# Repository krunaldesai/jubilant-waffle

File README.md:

# jubilant-waffle
HW/SW for PAC-USWHS002-WF-2 replacement based on m5stack AtomS3 mini and ESPhome

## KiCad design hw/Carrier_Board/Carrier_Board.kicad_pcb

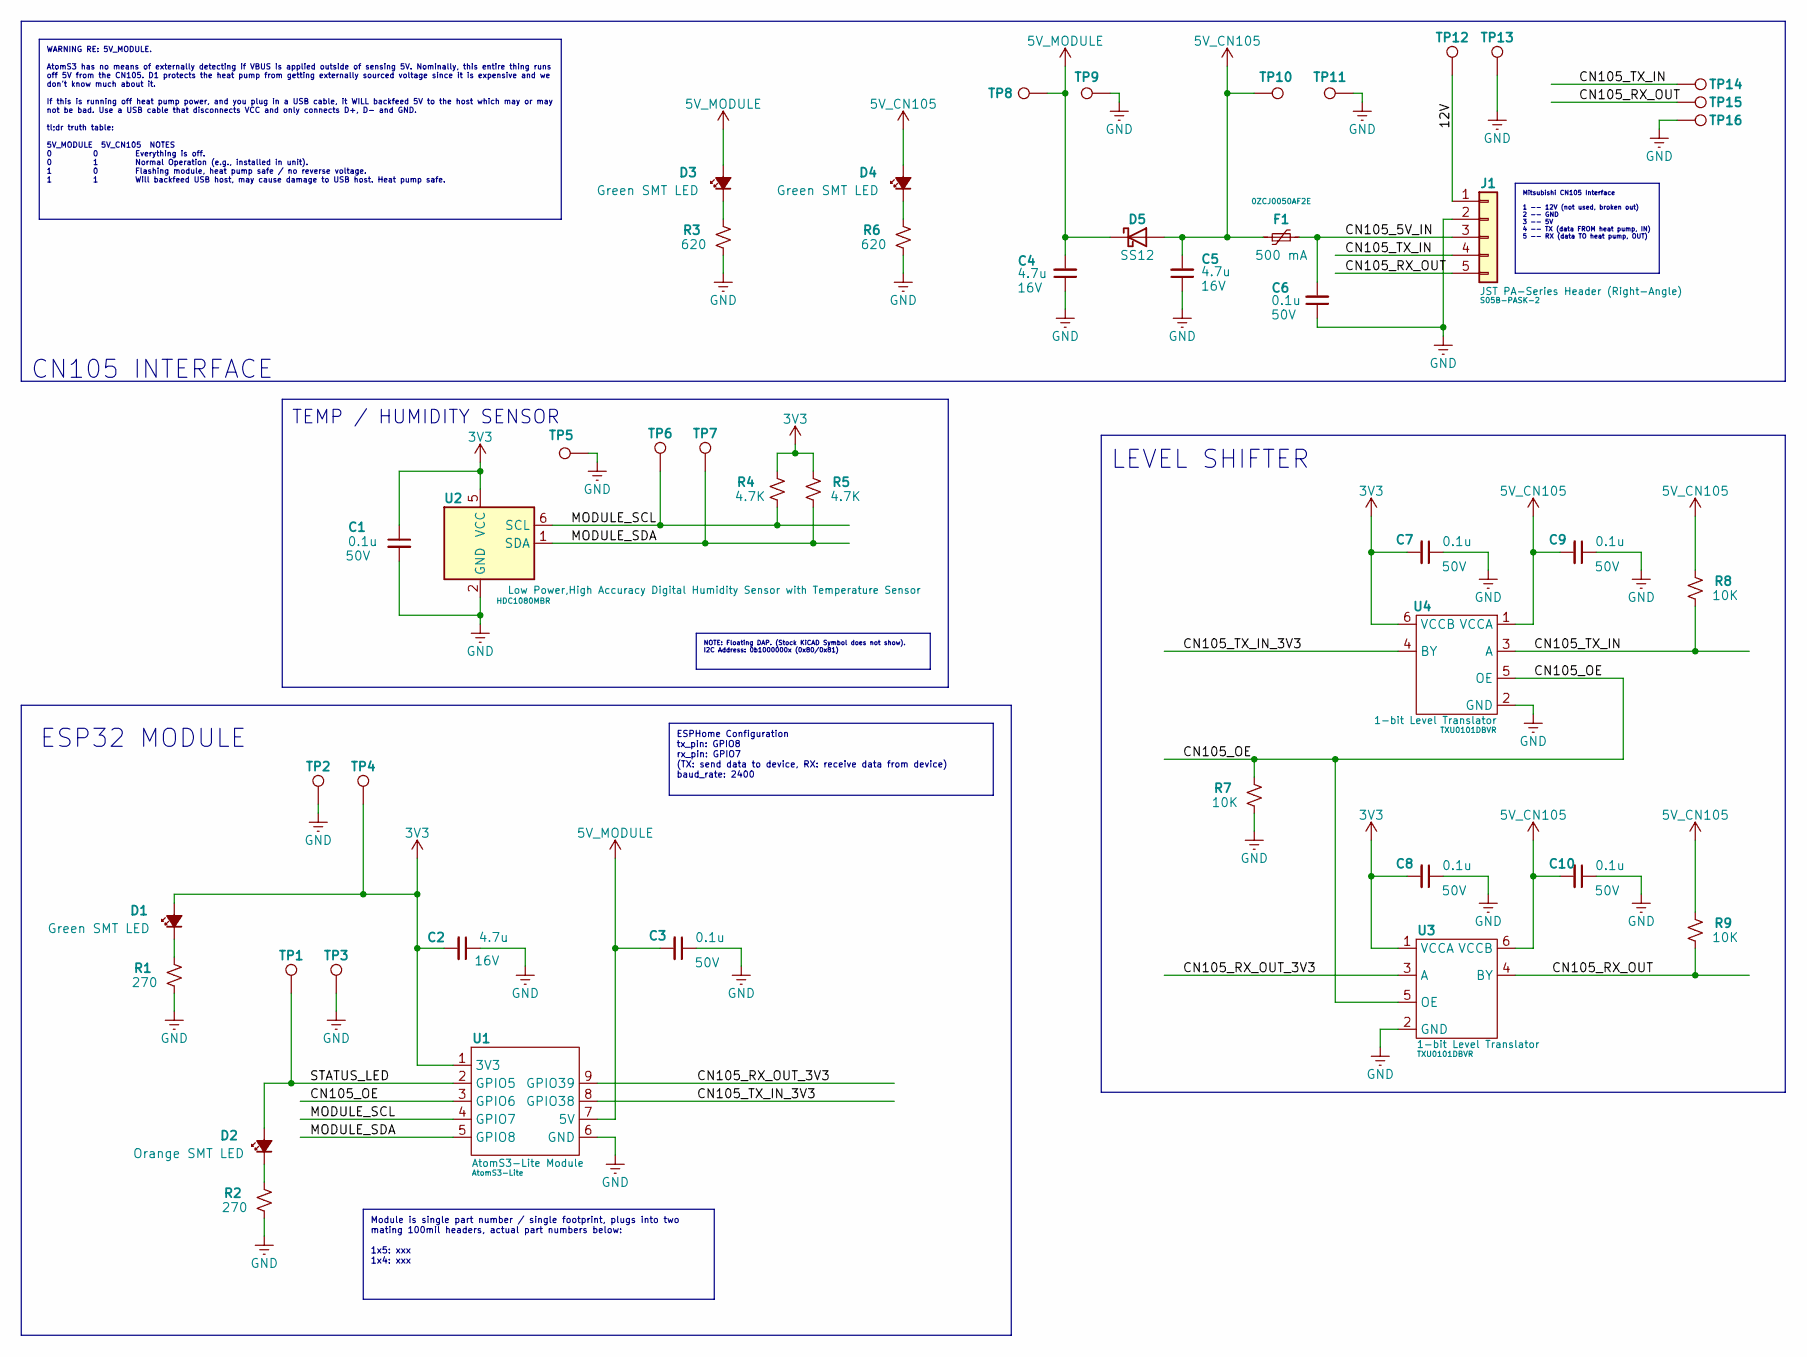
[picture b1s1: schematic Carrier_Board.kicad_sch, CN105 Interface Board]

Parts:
C1, C3, C6, C7, C8, C9, C10: 0.1u; C_0603_1608Metric_Pad1.08x0.95mm_HandSolder; Voltage 50V; ManufacturerPartNumber C0603C104K5RAC7411
C2, C4, C5: 4.7u; C_0805_2012Metric_Pad1.18x1.45mm_HandSolder; Voltage 16V; ManufacturerPartNumber GRM21BR71C475KE51L
D1, D3, D4: LED_Small_Filled; LED_0603_1608Metric_Pad1.05x0.95mm_HandSolder; ManufacturerPartNumber LTST-C190GKT
D2: LED_Small_Filled; LED_0603_1608Metric_Pad1.05x0.95mm_HandSolder; ManufacturerPartNumber LTST-C190AKT
D5: SS12; D_SMA; ManufacturerPartNumber SS12
F1: 500 mA; Fuse_1206_3216Metric_Pad1.42x1.75mm_HandSolder; ManufacturerPartNumber 0ZCJ0050AF2E
J1: JST PA-Series Header (Right-Angle); JST_PA_S05B; ManufacturerPartNumber S05B-PASK-2
R1, R2: 270; R_0603_1608Metric_Pad0.98x0.95mm_HandSolder; ManufacturerPartNumber ERJ-3GEYJ271V
R3, R6: 620; R_0603_1608Metric_Pad0.98x0.95mm_HandSolder; ManufacturerPartNumber ERJ-3GEYJ621V
R4, R5: 4.7K; R_0603_1608Metric_Pad0.98x0.95mm_HandSolder; ManufacturerPartNumber ERJ-3GEYJ472V
R7, R8, R9: 10K; R_0603_1608Metric_Pad0.98x0.95mm_HandSolder; ManufacturerPartNumber ERJ-3GEYJ103V
TP1, TP2, TP3, TP4, TP5, TP6, TP7, TP8, TP9, TP10, TP11, TP12, TP13, TP14, TP15, TP16: TestPoint; TestPoint_Keystone_5000-5004_Miniature
U1: Atom_S3-Lite; ManufacturerPartNumber AtomS3-Lite
U2: HDC1080; Texas_PWSON-N6; ManufacturerPartNumber HDC1080MBR
U3, U4: SOT-23-6_Handsoldering; ManufacturerPartNumber TXU0101DBVR

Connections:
3V3: C1.1, C2.2, C7.2, C8.2, D1.2 (A), R4.1, R5.1, TP4.1, U1.1 (3V3), U2.5 (VCC), U3.1 (VCCA), U4.6 (VCCB)
5V_CN105: C5.2, C9.2, C10.2, D4.2 (A), D5.2 (A), F1.1, R8.1, R9.1, TP10.1, U3.6 (VCCB), U4.1 (VCCA)
5V_MODULE: C3.2, C4.2, D3.2 (A), D5.1 (K), TP8.1, U1.7 (5V)
/12V: J1.1, TP12.1
/CN105_5V_IN: C6.2, F1.2, J1.3
/CN105_OE: R7.1, U1.3 (GPIO6), U3.5 (OE), U4.5 (OE)
/CN105_RX_OUT: J1.5, R9.2, TP15.1, U3.4 (BY)
/CN105_RX_OUT_3V3: U1.9 (GPIO39), U3.3 (A)
/CN105_TX_IN: J1.4, R8.2, TP14.1, U4.3 (A)
/CN105_TX_IN_3V3: U1.8 (GPIO38), U4.4 (BY)
/MODULE_SCL: R4.2, TP6.1, U1.4 (GPIO7), U2.6 (SCL)
/MODULE_SDA: R5.2, TP7.1, U1.5 (GPIO8), U2.1 (SDA)
/STATUS_LED: D2.2 (A), TP1.1, U1.2 (GPIO5)
GND: C1.2, C2.1, C3.1, C4.1, C5.1, C6.1, C7.1, C8.1, C9.1, C10.1, J1.2, R1.2, R2.2, R3.2, R6.2, R7.2, TP2.1, TP3.1, TP5.1, TP9.1, TP11.1, TP13.1, TP16.1, U1.6 (GND), U2.2 (GND), U3.2 (GND), U4.2 (GND)
unnamed: D1.1 (K), R1.1
unnamed: D2.1 (K), R2.1
unnamed: D3.1 (K), R3.1
unnamed: D4.1 (K), R6.1

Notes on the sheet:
LEVEL SHIFTER
TEMP / HUMIDITY SENSOR
ESP32 MODULE
CN105 INTERFACE
NOTE: Floating DAP. (Stock KiCAD Symbol does not show). I2C Address: 0b1000000x (0x80/0x81)
ESPHome Configuration tx_pin: GPIO8 rx_pin: GPIO7 (TX: send data to device, RX: receive data from device) baud_rate: 2400
Module is single part number / single footprint, plugs into two mating 100mil headers, actual part numbers below: 1x5: xxx 1x4: xxx
WARNING RE: 5V_MODULE. AtomS3 has no means of externally detecting if VBUS is applied outside of sensing 5V. Nominally, this entire thing runs off 5V from the CN105. D1 protects the heat pump from getting externally sourced voltage since it is expensive and we don't know much about it. If this is r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
Mitsubishi CN105 Interface 1 -- 12V (not used, broken out) 2 -- GND 3 -- 5V 4 -- TX (data FROM heat pump, IN) 5 -- RX (data TO heat pump, OUT)

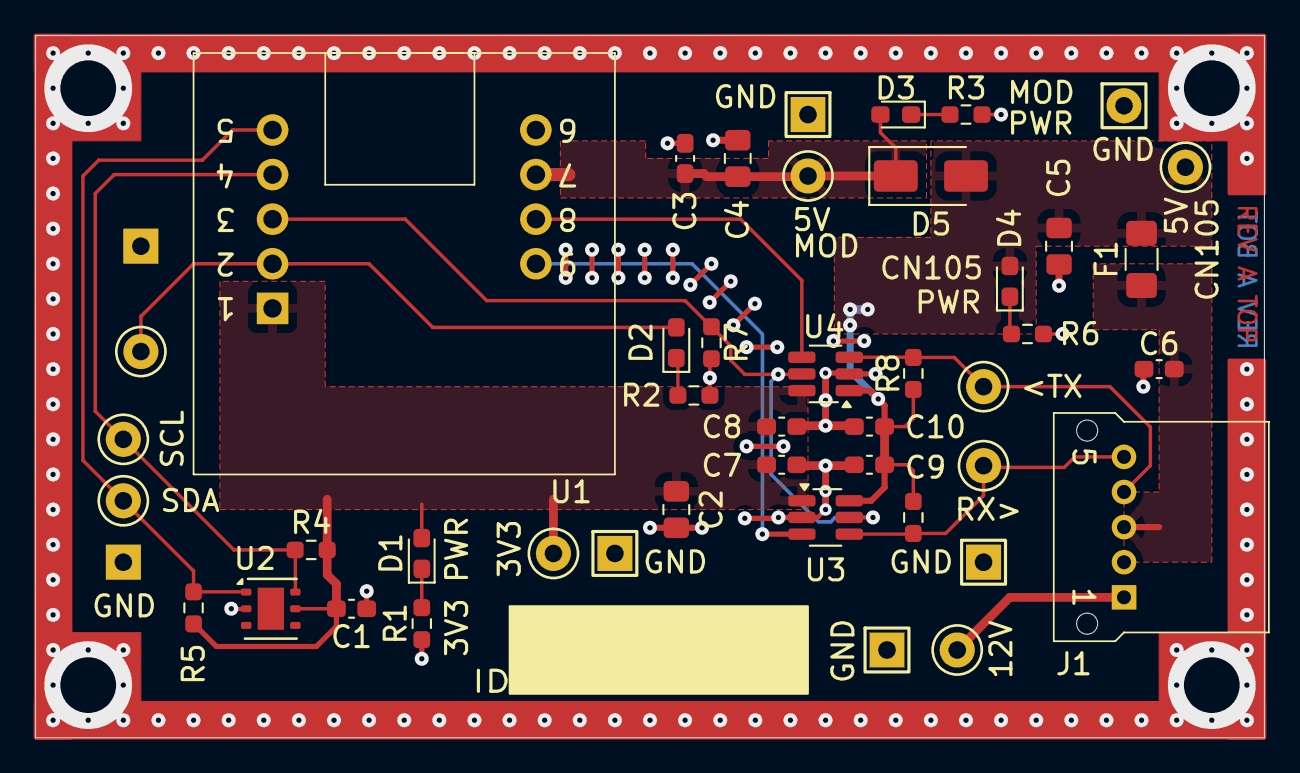
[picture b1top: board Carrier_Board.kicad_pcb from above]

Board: 2 copper layers, 70.0 x 40.0 mm, 46 parts (0 on the bottom side), 18 nets.

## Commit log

2025-01-23 hw: initial commit of first kicad project messing around
2025-02-09 hw: initial schematic mostly done, pushing for reference
2025-02-10 hw: initial layout done as well
2025-02-10 hw: ready for initial quoting
2025-02-10 hw: few little tweaks
2025-02-16 hw: revA for fab
